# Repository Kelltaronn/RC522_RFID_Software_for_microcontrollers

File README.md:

This files are the MFRC522 13.56 Mhz reader files which controlled by a Raspberry PI PICO microcontroller. The version1.0 is the current state of the project.

The keyboard layout of the hexdecimal keycode values.

0

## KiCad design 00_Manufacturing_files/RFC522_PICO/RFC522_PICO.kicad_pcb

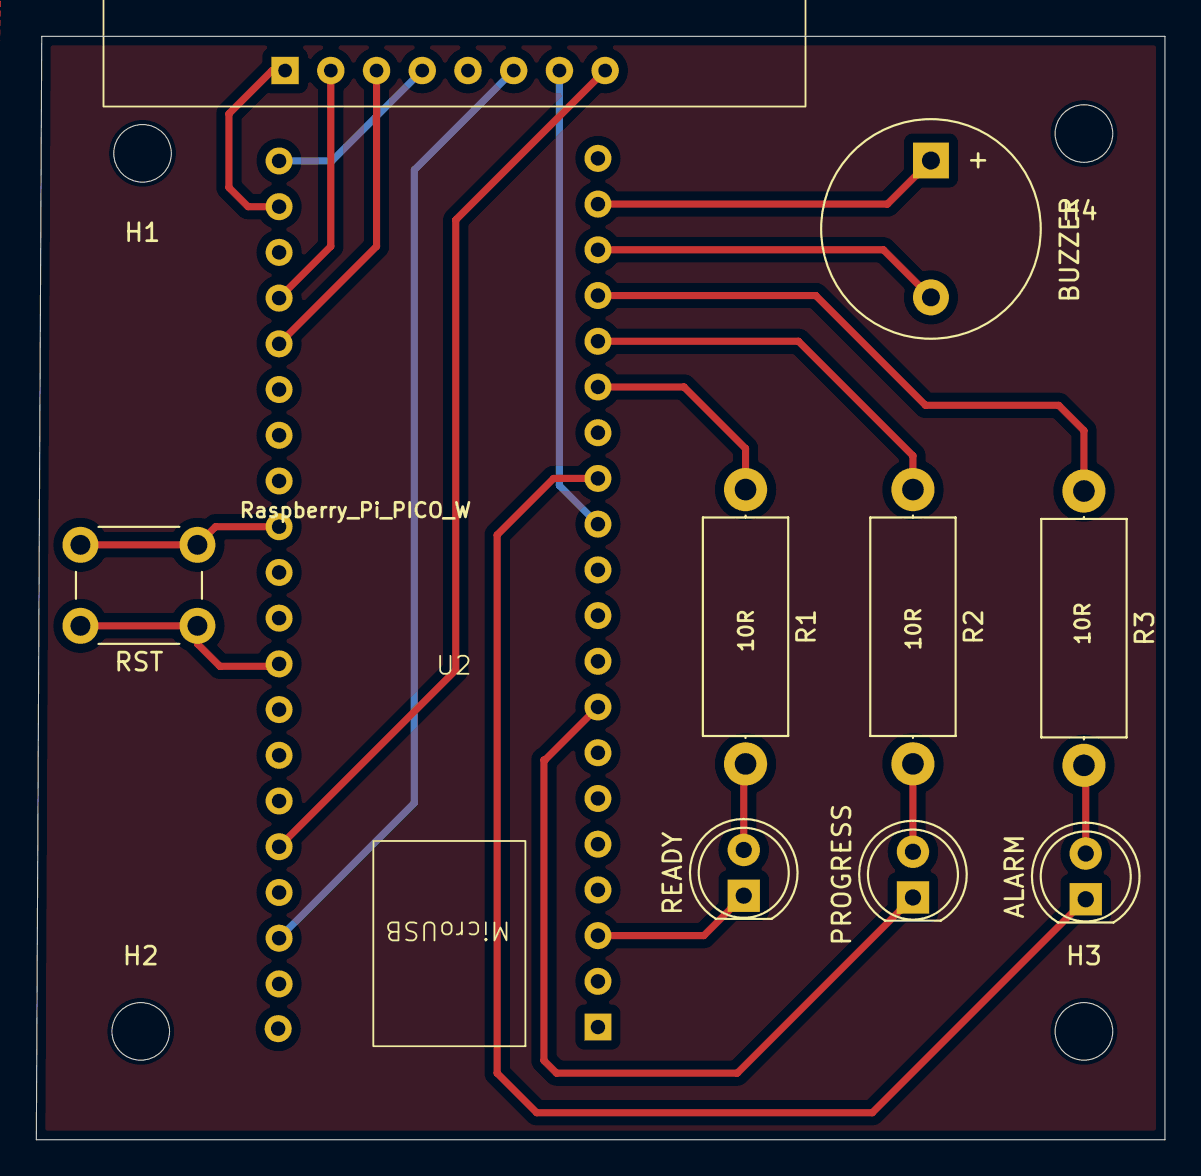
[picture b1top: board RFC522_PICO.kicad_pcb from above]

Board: 4 copper layers, 62.7 x 61.3 mm, 14 parts (0 on the bottom side), 20 nets.

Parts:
ALARM: LED; LED_D5.0mm
BUZZER: Buzzer; Buzzer_12x9.5RM7.6
H1, H2, H3, H4: MountingHole; MountingHole_3.2mm_M3
PROGRESS: LED; LED_D5.0mm
R1, R2, R3: 10R; R_Axial_DIN0414_L11.9mm_D4.5mm_P15.24mm_Horizontal
READY: LED; LED_D5.0mm
RST: SW_Push; SW_PUSH_6mm
U1: RFC522
U2: Raspberry_PI PICO; Raspberry Pico W

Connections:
unnamed: BUZZER.1 (+), U2.19 (GP14)
unnamed: BUZZER.2 (-), U2.18 (GND)
unnamed: R1.2, READY.2 (A)
unnamed: READY.1 (K), U2.3 (GND)
unnamed: ALARM.2 (A), R3.2
unnamed: ALARM.1 (K), U2.13 (GND)
unnamed: U1.6 (GND), U2.23 (GND)
unnamed: U1.4 (MISO), U2.40 (GP16)
unnamed: U1.3 (MOSI), U2.36 (GP19)
unnamed: U1.7 (RST), U2.12 (GP9)
unnamed: U1.2 (SCK), U2.37 (GP18)
unnamed: U1.1 (SDA), U2.39 (GP17)
unnamed: U1.8 (VCC_3.3V), U2.25 (3V3(OUT))
unnamed: R1.1, U2.15 (GP11)
unnamed: R2.1, U2.16 (GP12)
unnamed: R3.1, U2.17 (GP13)
unnamed: RST.2, U2.32 (GP22)
unnamed: RST.1, U2.29 (GP27)
unnamed: PROGRESS.2 (A), R2.2
unnamed: PROGRESS.1 (K), U2.8 (GND)

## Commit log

2026-01-27 first_software_version
2026-01-27 version1.1
2026-01-27 version1.1_Encryption_Decryption
2026-01-27 Base_secret_key_loading
2026-01-28 rebase_test
2026-01-28 Secret.txt
2026-01-28 Changed_logging_for_faster_log_test
2026-01-29 README.md changes
2026-04-07 Deleting and cleaning unnessecary files
2026-04-13 GUI_development_start
2026-04-14 Serial_communication
2026-04-14 GUI_Serial_modification
2026-04-23 Organizing Architecture
2026-06-30 PCB drawings
